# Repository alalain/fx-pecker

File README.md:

# FX Pecker

Audio FX plattform for a Raspberry PI with
a 6.3mm analog mono input and 6.3mm analog mono output.

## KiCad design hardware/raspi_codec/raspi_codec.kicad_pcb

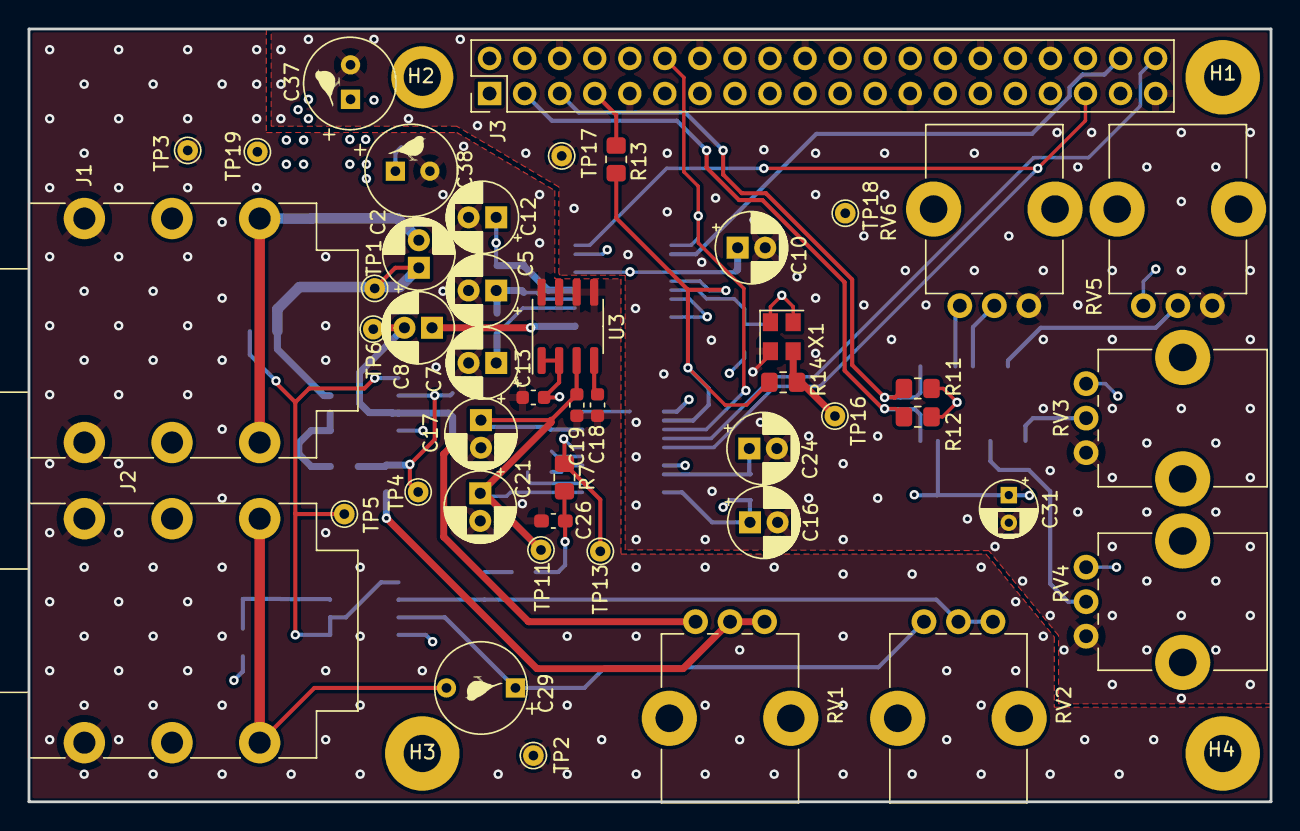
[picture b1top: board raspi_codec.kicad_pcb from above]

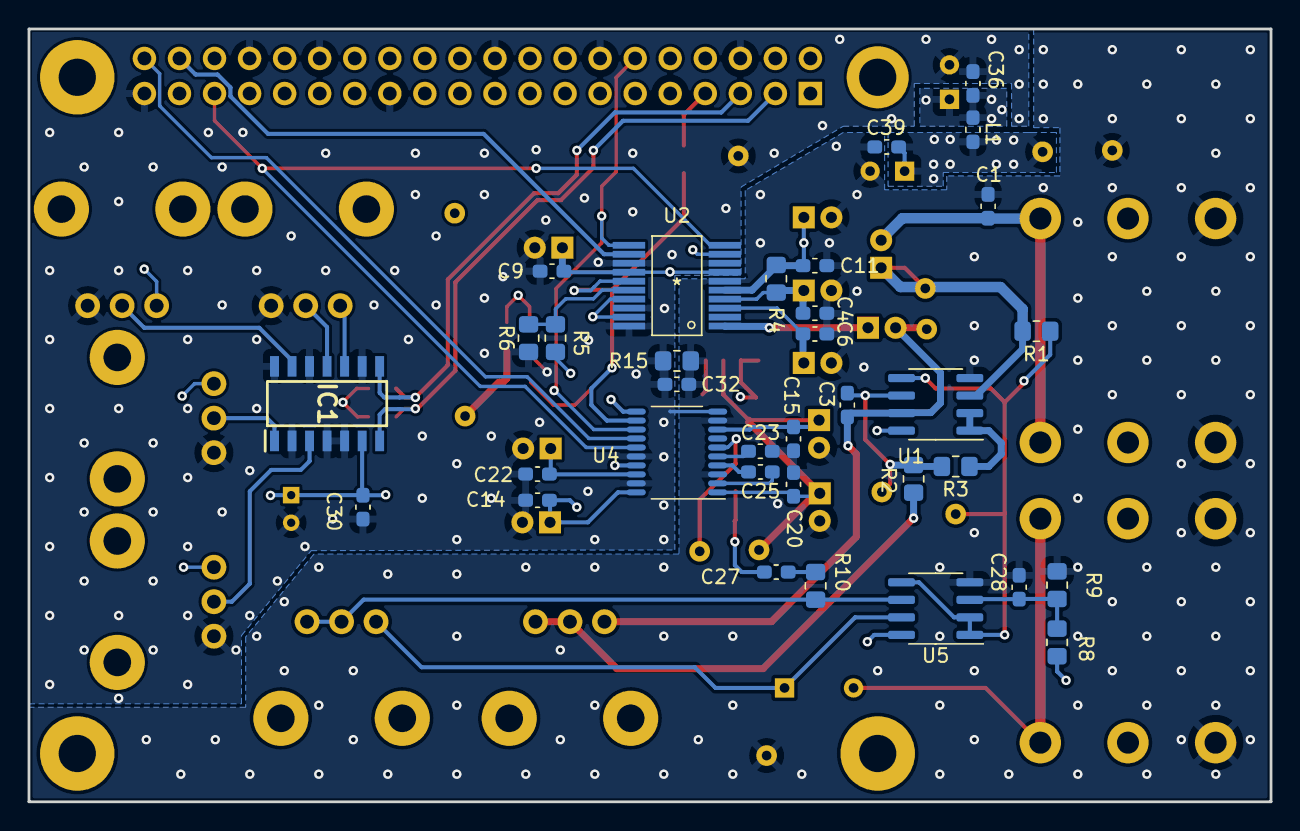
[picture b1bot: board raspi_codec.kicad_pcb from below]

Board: 4 copper layers, 90.0 x 56.0 mm, 84 parts (34 on the bottom side), 42 nets.

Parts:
C1, C3, C32: C; C_0603_1608Metric_Pad1.08x0.95mm_HandSolder
C2, C5, C7, C10, C12, C16, C17, C21, C24: 10u; CP_Radial_D5.0mm_P2.00mm
C4, C6, C9, C11, C14, C15, C20, C22, C30: 0.1u; C_0603_1608Metric_Pad1.08x0.95mm_HandSolder
C8: 1u; CP_Radial_D5.0mm_P2.00mm
C13: 1u; C_0603_1608Metric
C18: 100p; C_0603_1608Metric
C19: 2u; C_0603_1608Metric
C23, C25: 2.2u; C_0603_1608Metric_Pad1.08x0.95mm_HandSolder
C26: 2.2n; C_0603_1608Metric_Pad1.08x0.95mm_HandSolder
C27: C_Polarized; C_0603_1608Metric_Pad1.08x0.95mm_HandSolder
C28: 10n; C_0603_1608Metric_Pad1.08x0.95mm_HandSolder
C29: 100u; CP_RADIAL_6.3mm_5mm
C31: 10u; CP_Radial_D4.0mm_P2.00mm
C36, C39: 100n; C_0603_1608Metric_Pad1.08x0.95mm_HandSolder
C37, C38: 100u; CP_RADIAL_6.3mm_2.5mm
H1, H2, H3, H4: MountingHole; MountingHole_2.7mm_Pad
IC1: MCP3428-E_SL; SOIC127P600X175-14N
J1, J2: AudioJack3_Switch; jack_raspi_6.3mmjack
J3: Conn_02x20_Top_Bottom_MountingPin; PinHeader_2x20_P2.54mm_Vertical
L1: 10u; L_0603_1608Metric_Pad1.05x0.95mm_HandSolder
R1: 900k; R_0805_2012Metric_Pad1.20x1.40mm_HandSolder
R2: 10k; R_0805_2012Metric_Pad1.20x1.40mm_HandSolder
R3, R10: 20k; R_0805_2012Metric_Pad1.20x1.40mm_HandSolder
R4: 1k; R_0805_2012Metric_Pad1.20x1.40mm_HandSolder
R5, R6, R11, R12, R13, R14, R15: R; R_0805_2012Metric_Pad1.20x1.40mm_HandSolder
R7: 470; R_0805_2012Metric_Pad1.20x1.40mm_HandSolder
R8, R9: 100k; R_0805_2012Metric_Pad1.20x1.40mm_HandSolder
RV1, RV2: 100k Log; Potentiometer_Bourns_PTV09A-1_Single_Vertical
RV3, RV4, RV5, RV6: 100k; Potentiometer_Bourns_PTV09A-1_Single_Vertical
TP1, TP2, TP3, TP4, TP5, TP6, TP11, TP13, TP16, TP17, TP18, TP19: TestPoint; TestPoint_THTPad_D1.5mm_Drill0.7mm
U1, U5: MCP6L02x-xSN; SOIC-8_3.9x4.9mm_P1.27mm
U2: PCM1802DB
U3: MIC5219-3.3YMM; SOIC-8_3.9x4.9mm_P1.27mm
U4: PCM5102APW
X1: ASE-24.576MHz; Oscillator_SMD_Abracon_ASE-4Pin_3.2x2.5mm

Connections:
/ADC/ADC_IN: C8.1, U2.1 (VINL)
/DAC/DAC_OUT: R7.1, TP13.1, U4.6 (OUTL)
/DAC/Out: C29.2, J2.S, J2.SN
/DAC/VMID_UNBUF: C28.1, R8.2, R9.1, U5.3 (+)
/Input Stage/BufferIn: C2.1, R1.2, TP1.1, U1.3 (+)
/Input Stage/IN: C1.1, C2.2, J1.S, J1.SN
/Input Stage/PreAmpNeg: C3.1, R2.2, R3.2, TP4.1, U1.6 (-)
/connection/CLK_OZ: R14.1, TP16.1, X1.3 (OUT)
/connection/CLK_RP: J3.7, R13.1
AN_in1: C3.2, C8.2, RV1.1, TP6.1, U1.7
AVDD: C15.1, C17.1, C19.1, C20.1, C21.1, TP11.1, U3.3 (OUT), U4.1 (CPVDD), U4.8 (AVDD)
GNDA: C1.2, C4.1, C5.2, C6.1, C7.2, C11.1, C12.2, C13.2, C15.2, C17.2, C18.2, C19.2, C20.2, C21.2, C23.2, C26.1, C28.2, C32.1, C38.2, C39.2, J1.T, J1.TN, J2.T, J2.TN, R9.2, R15.2, TP2.1, TP3.1, U1.4 (V-), U2.6 (AGND), U3.5 (GND), U3.6 (GND), U3.7 (GND), U3.8 (GND), U4.3 (CPGND), U4.9 (AGND), U5.4 (V-)
GNDD: C9.1, C10.2, C14.2, C16.2, C22.2, C24.2, C30.2, C31.2, C32.2, C36.2, C37.2, IC1.2 (CH1-), IC1.4 (CH2-), IC1.5 (VSS), IC1.9 (ADR0), IC1.12 (CH3-), IC1.14 (CH4-), J3.6, J3.9, J3.14, J3.20, J3.25, J3.30, J3.34, J3.39, R6.2, R15.1, RV3.1, RV4.1, RV5.1, RV6.1, TP17.1, U2.8 (BYPAS), U2.13 (DGND), U2.18 (FMT1), U2.20 (MODE1), U4.10 (DEMP), U4.16 (FMT), U4.19 (DGND), X1.2 (GND)
I2S_CLK: J3.12, U2.11 (BCK), U4.13 (BCK)
I2S_DIN: J3.38, U2.12 (DOUT)
I2S_DOUT: J3.40, U4.14 (DIN)
I2S_FS: J3.35, U2.10 (LRCK), U4.15 (LRCK)
LDOO: C22.1, C24.1, U4.18 (LDOO)
unnamed: C18.1, U3.4 (BP)
unnamed: C25.1, U4.4 (CAPM)
unnamed: C25.2, U4.2 (CAPP)
unnamed: C26.2, C27.2, R7.2
unnamed: C27.1, R10.1
unnamed: C29.1, RV2.1, U5.7
unnamed: IC1.1 (CH1+), RV3.2
unnamed: IC1.3 (CH2+), RV4.2
unnamed: IC1.11 (CH3+), RV6.2
unnamed: IC1.13 (CH4+), RV5.2
unnamed: R2.1, RV1.2, RV1.3
unnamed: R3.1, U1.1, U1.2 (-)
unnamed: R5.2, R6.1, U2.16 (OSR)
unnamed: R10.2, RV2.2, RV2.3, U5.6 (-)
SCL: IC1.8 (SCL), J3.5, R11.1
SCLK: R13.2, R14.2, U2.15 (SCKI), U4.12 (SCK)
SDA: IC1.7 (SDA), J3.3, R12.1
VCC: C11.2, C12.1, C13.1, C38.1, C39.1, L1.2, R4.1, R8.1, TP19.1, U1.8 (V+), U2.5 (VCC), U3.1 (EN), U3.2 (IN), U5.8 (V+)
VCCD: C36.1, C37.1, J3.2, J3.4, L1.1
VDD: C9.2, C10.1, C14.1, C16.1, C30.1, C31.1, IC1.6 (VDD), IC1.10 (ADR1), J3.1, J3.17, R5.1, R11.2, R12.2, RV3.3, RV4.3, RV5.3, RV6.3, TP18.1, U2.7 (PDWN_N), U2.9 (FSYNC), U2.14 (VDD), U2.17 (FMT0), U2.19 (MODE0), U4.11 (FLT), U4.17 (XSMT), U4.20 (DVDD), X1.1 (EN), X1.4 (Vdd)
VMID: R1.1, TP5.1, U1.5 (+), U5.1, U5.2 (-), U5.5 (+)
VNEG: C23.1, U4.5 (VNEG)
VREF1: C6.2, C7.1, U2.3 (VREF1)
VREF2: C4.2, C5.1, R4.2, U2.4 (VREF2)

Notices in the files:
parts and their libraries:
Copyright 2021 Accelerated Designs. All rights reserved.
